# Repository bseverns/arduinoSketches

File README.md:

# Arduino Sketchbook Field Guide

Welcome to the synth lab slash robot garage. This repo is a studio notebook of quick-and-dirty experiments, but now it has a map. Use this README like a zine—skim the spreads, pick a neighborhood, and dive in with intent.

## How this sketchbook is organized
Each folder is an Arduino sketch directory. Drop one into your `sketchbook/` and the IDE will treat it as its own project. Libraries such as **Mozzi** or **Adafruit WaveHC** must already be installed in your Arduino environment.

The collections below are loose crews, not rigid taxonomies; if you discover better alignments, remix away.

If you want to organize by **progression instead of genre**, use [`docs/progression-map.md`](docs/progression-map.md). That map groups folders into likely family lines such as `greyBox_*`, `mozzi_5knob*`, `SKY_PHONE_*`, and other sketch evolutions, which is the safest way to start cleaning a repo this flat.

## New Top-Level Structure
- `experiments/`
  - Families of sketches that clearly represent iterative work.
- `projects/`
  - More complete or installation-oriented builds that have progressed beyond sketch experiments.
- `holding/`
  - Intentionally unspecific buckets for sketches worth keeping together before a better taxonomy is obvious.
- `archive/`
  - Legacy branches and older finished variants that should stay available without dominating the main map.
- `third_party/reference/`
  - Imported libraries, vendor code, and upstream projects kept for reference.
- repo root
  - Legacy standalone sketches and projects that have not been grouped yet.

### Synthesis & Sound Design
Projects that cook tones directly on the microcontroller.
- `experiments/synthesis/mozzi-controls/5knob_MozziSynth/`, `experiments/synthesis/mozzi-controls/mozzi_5knob/`, `experiments/synthesis/mozzi-controls/mozzi_5knob_L/`, `experiments/synthesis/mozzi-controls/mozzi_5knob_L_GB/`, `mozziSynth_glitch/`
  - Mozzi-powered sketches covering FM, glitchy filters, multi-knob control, and the cleaned-up FM showcase in this repo.
- `experiments/synthesis/attiny85-sound/attiny85_random_burst_drone/`, `experiments/synthesis/attiny85-sound/attiny85_dual_clock_clash/`, `experiments/synthesis/attiny85-sound/attiny85_quad_xor_drone/`,
  `experiments/synthesis/attiny85-sound/attiny85_pitch_ramp_randomizer/`, `experiments/synthesis/attiny85-sound/attiny85_three_voice_gate/`, `experiments/synthesis/attiny85-sound/attiny85_scale_sequencer/`,
  `experiments/synthesis/attiny85-sound/attiny85_random_pwm_noise/`, `experiments/synthesis/attiny85-sound/attiny85_pitch_mutator/`, `experiments/synthesis/attiny85-sound/attiny85_drum_trax/`
  - Bare-metal ATTiny85 tone experiments rescued from hash-folders; expect raw timer hacking and button-driven chaos.
- `experiments/synthesis/auduino/auduino/`, `experiments/synthesis/auduino/auduino_v5/`, `experiments/synthesis/auduino/AuduinoSequencer/`
  - Classic granular/noise textures and sequencer riffs.
- `granularSynth/`, `pdVCO/`, `avrPitchSampler/`
  - More experimental oscillators and pitch shifters.

### Samplers, Players & Shields
Boards that sling prerecorded audio or lean on helper hardware.
- `WAVshield/`, `PING_WAV/`, `Ping_baby/`, `PIR_soundie/`
  - SD-card playback patterns, button routing, and motion-triggered samples.
- `experiments/playback/sample-players/SamplerUnoPlayer/`, `experiments/playback/sample-players/SamplerUnoPlayer_test/`, `SampleRateMod/`, `sampleLauncher_neotrellis/`
  - Quick-loading sample players, rate changers, and the NeoTrellis launcher.
- `tiny85audioplayer/`
  - Tiny microcontroller players when you’re short on pins and patience.

### Sensors, Triggers & I/O
- `experiments/sensors-actuators/Blink_baby/`, `experiments/sensors-actuators/trinketInstall_baby/`, `experiments/sensors-actuators/lineIn/`, `experiments/sensors-actuators/baby_switch/`
  - Small hardware-facing sketches for trigger tests, sensor input, actuator output, and early switch prototypes.

### Rhythm, Sequencers & Generative Gizmos
Keep time, break time, or let the machine improvise.
- `experiments/sequencers/ArduinoPunk/`, `experiments/sequencers/SimpleZAR/`, `experiments/sequencers/sixteen_step_sequencer/`
  - Step-sequencer builds with explicit pattern editing, clocking, or step-based control.
- `experiments/algorithms/generativeAlgoSound/`, `experiments/algorithms/oneLineAlgo/`, `experiments/algorithms/_2noise/`
  - Algorithm-first audio and visual studies.
- `experiments/rhythm-boxes/drum8/`, `experiments/rhythm-boxes/ANDI-master/`
  - Drum-machine and loop-box style builds that are rhythm-led but not primarily note sequencers.
- `experiments/playback/shield-players/player_simple_shieldVersion/`, `experiments/playback/shield-players/player_interrupts_ShieldVersion/`
  - IRQ-friendly players useful for tempo-locked sample chops.

### Holding Area
- `holding/uncategorized/glitchamin/`, `holding/uncategorized/Musicator/`, `holding/uncategorized/mP1/`, `holding/uncategorized/IllutronBDemo0_2/`, `holding/uncategorized/Jingle_Hell__Saturnalia_/`, `holding/uncategorized/MozziSynth_example1/`
  - Real sketches worth keeping together, but not yet sorted into a more defensible family.
- `holding/modern-platformio-demos/moarknobs_button_ef_usb_midi_demo/`, `holding/modern-platformio-demos/diceloop_rough_prototype/`, `holding/modern-platformio-demos/hallway_reactor_2m/`, `holding/modern-platformio-demos/linelight_band_lamp/`, `holding/modern-platformio-demos/motorlightsound_lane_controller/`
  - Newer PlatformIO-era controller, sensor, and prototype snapshots imported from sibling repos for archival preservation before a stronger taxonomy is obvious.
- `holding/modern-platformio-demos/dust_press_minimal/`, `holding/modern-platformio-demos/horizon_minimal/`, `holding/modern-platformio-demos/rhythm_weave_minimal/`, `holding/modern-platformio-demos/tide_engine_minimal/`, `holding/modern-platformio-demos/orbit_looper_minimal/`, `holding/modern-platformio-demos/silt_minimal/`
  - Minimal Teensy Audio demo surfaces imported from sibling repos so the archive captures the small public-facing sketches as well as the larger firmware projects.
- `holding/modern-platformio-demos/dust_press_presets_demo/`, `holding/modern-platformio-demos/horizon_preset_morph/`, `holding/modern-platformio-demos/horizon_scope_demo/`, `holding/modern-platformio-demos/tide_engine_teaching_rig/`, `holding/modern-platformio-demos/tide_engine_humanize_demo/`
  - Richer teaching and bench-demo sketches imported from sibling repos once the minimal entrypoints were already preserved.

### Robotics, Kinetics & Control Surfaces
Anything that moves, senses, or bosses motors around.
- `drawBots/`, `drawBots_1/`
  - Button handling patterns and motion control for pen-plotter style bots.
- `dc_motor.ino` inside `drawBots/`, `experiments/robotics/robot-builds/realDRobot/`, `experiments/greybox/greyBox_Growser/`*
  - Reversible H-bridge driving and relay logic for more industrial builds.
- `experiments/robotics/robot-builds/OurRobot_1/`, `experiments/robotics/robot-builds/Our_Robot_01/`, `experiments/robotics/robot-builds/realDRobot/`, `experiments/robotics/relay-control/dbMSr3/`, `experiments/robotics/relay-control/dbSabertoothshield_1/`, `experiments/robotics/relay-control/dbrough/`, `experiments/robotics/relay-control/sP_relay1/`, `experiments/robotics/relay-control/sP_relay2/`, `experiments/robotics/relay-control/sP_relay3/`
  - Robot builds, relay control, and motor-driver experiments that fit better as families than one-offs.

### Named Projects & Installs
- `projects/interactive-installs/energy-light/ENERGY_1/`, `projects/interactive-installs/energy-light/Energy_TEST/`, `projects/interactive-installs/energy-light/Energy_FADE/`
  - A staged light/install line with clear progression in the names.
- `projects/interactive-installs/sky-phone/SKY_PHONE_2/`, `projects/interactive-installs/sky-phone/SKY_PHONE_FIN/`, `projects/interactive-installs/thesis-light/thesisLight/`, `projects/interactive-installs/thesis-light/thesisLightCTRL/`
  - Named installations or more complete interactive builds.
- `projects/personal-builds/mim/MiM_1/`, `projects/personal-builds/sproject/Sproject_1/`
  - Prior personal projects that belong in the project layer rather than the experiment layer.

### Reference Dumps & Vendor Libraries
- `third_party/reference/AdafruitAudio-master/`, `third_party/reference/Adafruit_NeoTrellisM4-master/`, `third_party/reference/Arduinoboy-master/`, `third_party/reference/jan_ostmans_synths-master/`
  - Mostly upstream copies; treat them as reference manuals.
- `third_party/reference/DuinoTune-master/`, `third_party/reference/PJRCAudio-master/`, `third_party/reference/AttinySound-master/`, `third_party/reference/Mozzi/`, `third_party/reference/wavehc/`
  - Utility toolkits that underpin several sketches.

### Notes, Docs & Ephemera
- `docs/`
  - Former stray PDFs now corralled into a single folder.
  - See `docs/showcase.md` for wiring guides + BOMs on the crowd-pleasers.
- `Notes_keke_siren/`, `ReferanceSketch/`, `projects/interactive-installs/sky-phone/SKY_PHONE_2/`, `projects/interactive-installs/sky-phone/SKY_PHONE_FIN/`
  - Mixed notes and iterations. Expect loose ends.
- `archive/legacy-finals/son-build/The_Son_final/`, `archive/legacy-finals/son-build/The_Son_final_a/`
  - Older final-branch snapshots kept around for history, not active browsing.

\* Many of these builds assume external motor drivers, relays, or sensors. Read the header comments in each sketch for wiring specifics before soldering anything permanent.

## Quick-start checklists
1. **Pick a theme above** and copy that folder to your Arduino sketchbook.
2. **Install dependencies** (Mozzi, WaveHC, Sabertooth, etc.) via the Arduino Library Manager or from the copies in `third_party/reference/`.
3. **Check pin assignments** in the `.ino` file comments and adjust for your hardware.
4. **Prototype fast**. This is a playground—fork the sketch, twist a knob, record what happens.

## Where to explore next
- Tighten the best-performing sketches into showcase-ready demos with photos or wiring diagrams. `docs/showcase.md` has TODO slots waiting for media drops.
- Document unexpected tricks (timer sharing, ISR gotchas) directly in the sketches.
- Trade polished recordings for commit history: drop audio snippets or GIFs into `docs/` to complement the code. Call your shot with TODO notes until the binary files land.
- Keep moving low-ambiguity families first; leave one-off sketches at the repo root until the domain or lineage is actually clear.

Questions? Crack open the serial monitor, read the comments, and don’t be afraid to get weird—but keep it useful.

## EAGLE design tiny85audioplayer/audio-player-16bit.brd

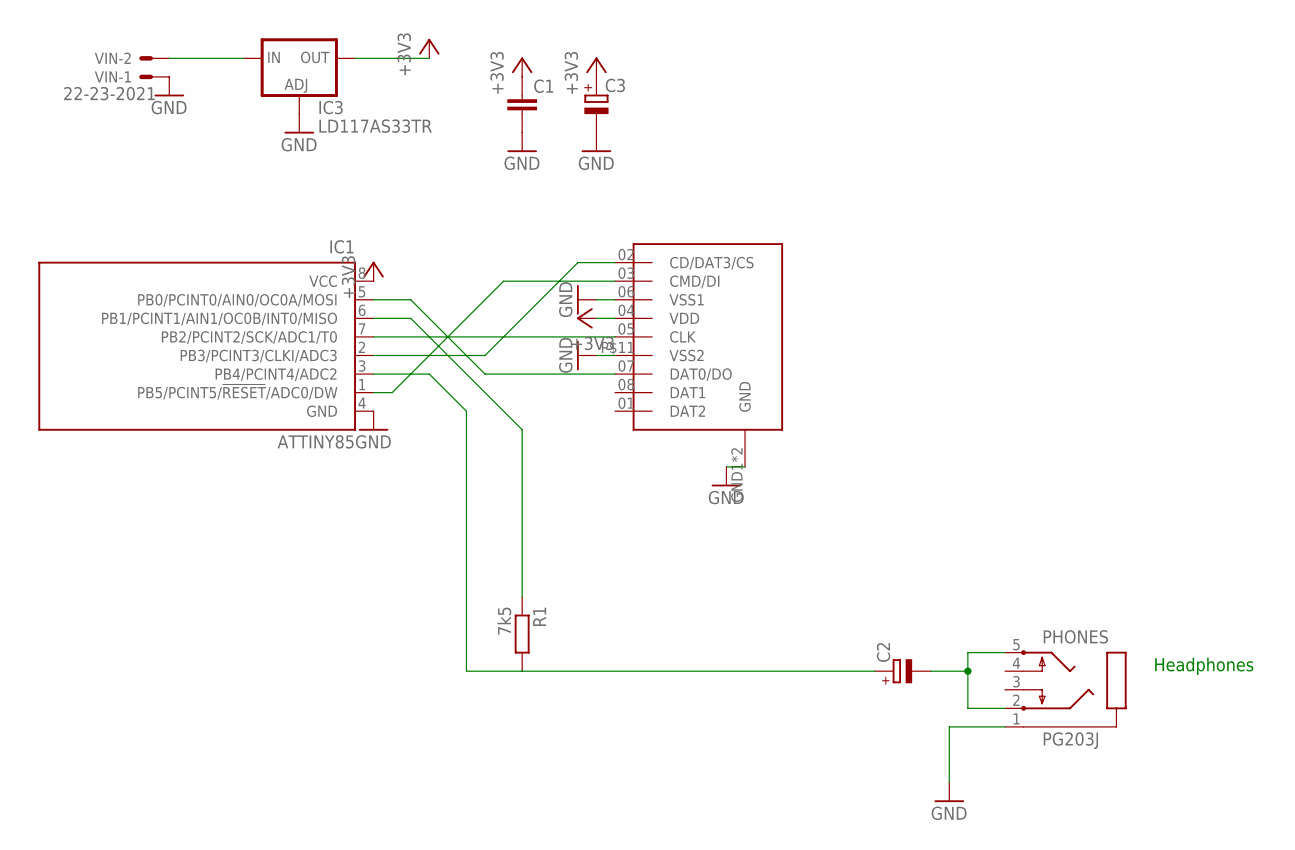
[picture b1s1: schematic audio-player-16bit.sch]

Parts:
C1: C-EUC1206; C1206
C2: CPOL-EU140CLH-1014; 140CLH-1014
C3: CPOL-EUCT3528; CT3528
IC1: ATTINY85; DIL08
IC3: LD117AS33TR; SOT223
PHONES: PG203J
R1: 7k5; R1206
U$1: MICROSD; SCHD3A0100
VIN: 22-23-2021

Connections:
+3V3: C1.1, C3.+, IC1.8 (VCC), IC3.4 (OUT), U$1.04 (VDD)
GND: C1.2, C3.-, IC1.4 (GND), IC3.1 (ADJ), PHONES.1, U$1.06 (VSS1), U$1.GND1 (GND), U$1.GND2 (GND), U$1.P$11 (VSS2), VIN.1
unnamed: IC1.2 (PB3/PCINT3/CLKI/ADC3), U$1.02 (CD/DAT3/CS)
unnamed: IC1.6 (PB1/PCINT1/AIN1/OC0B/INT0/MISO), R1.1
unnamed: IC1.7 (PB2/PCINT2/SCK/ADC1/T0), U$1.05 (CLK)
unnamed: C2.+, IC1.3 (PB4/PCINT4/ADC2), R1.2
unnamed: IC1.1 (PB5/PCINT5/!RESET!/ADC0/DW), U$1.03 (CMD/DI)
unnamed: IC1.5 (PB0/PCINT0/AIN0/OC0A/MOSI), U$1.07 (DAT0/DO)
unnamed: IC3.3 (IN), VIN.2
unnamed: C2.-, PHONES.2, PHONES.5

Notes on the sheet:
Headphones

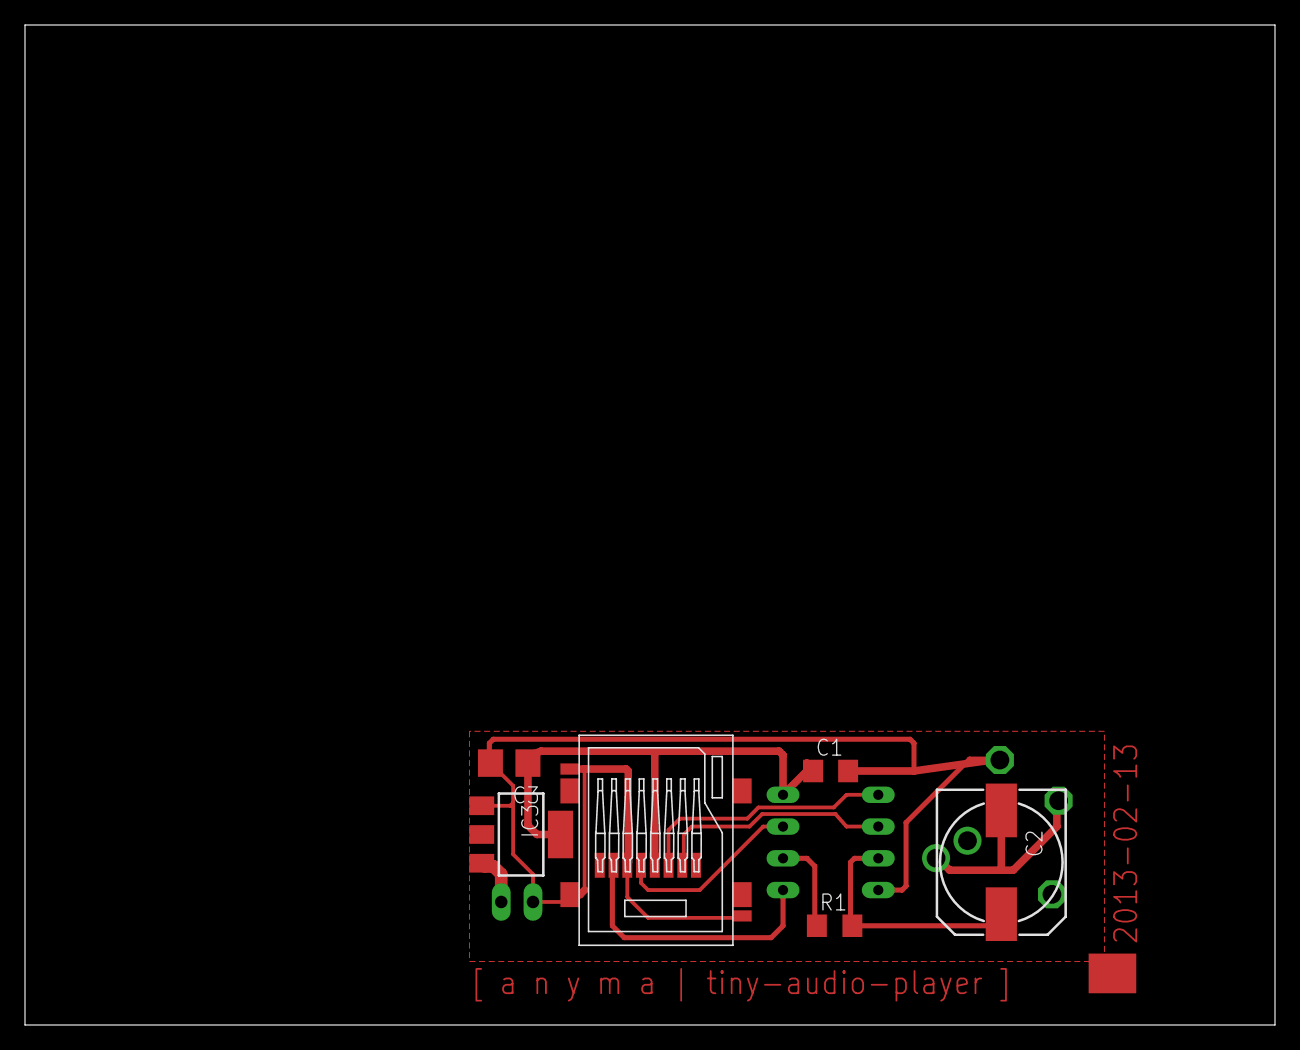
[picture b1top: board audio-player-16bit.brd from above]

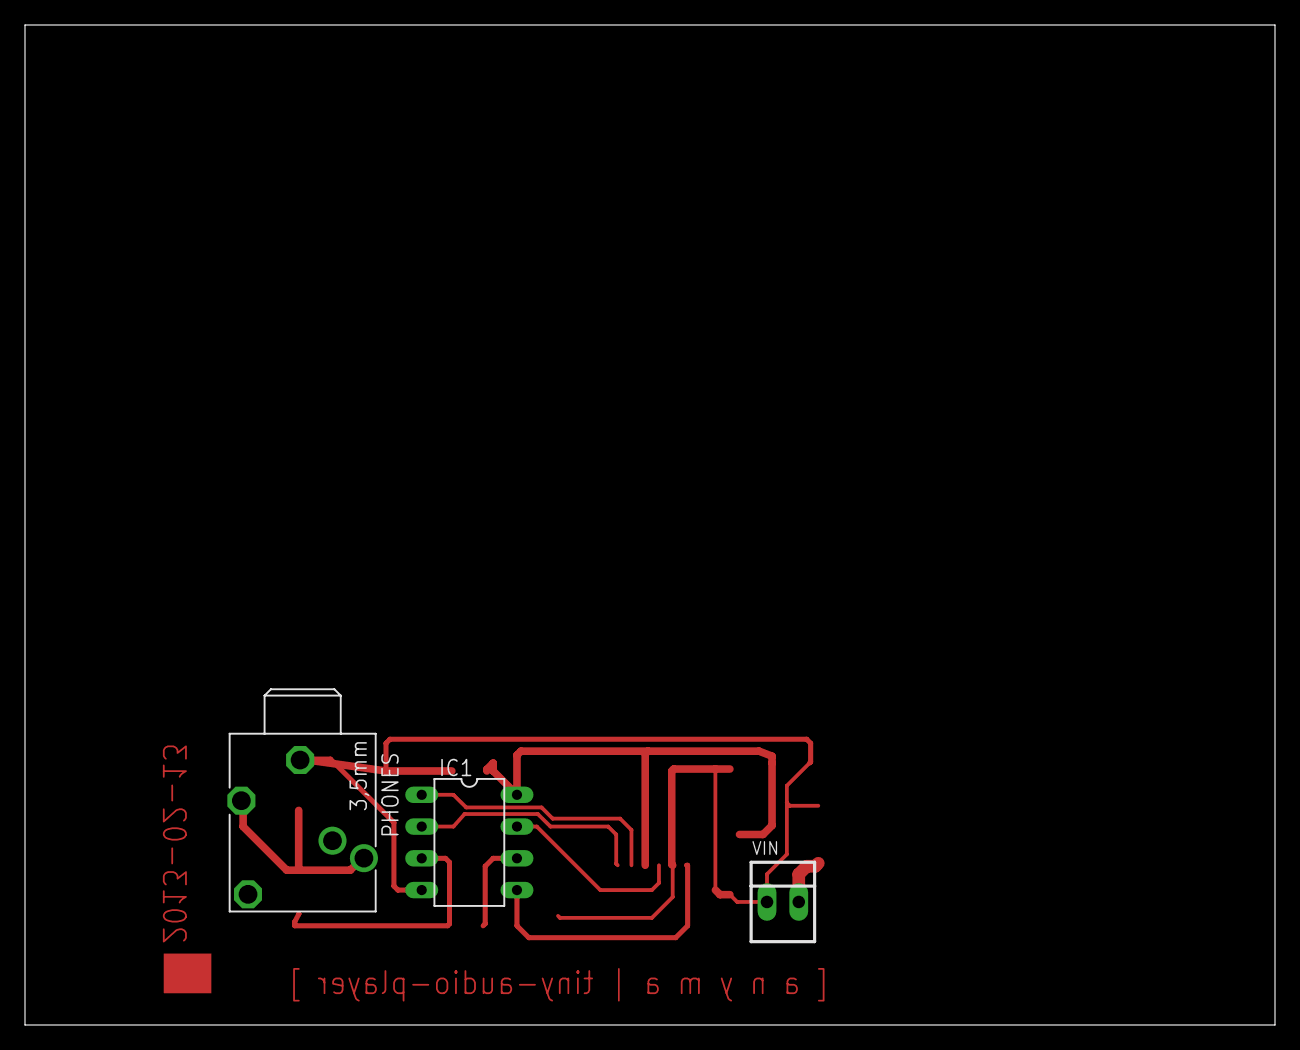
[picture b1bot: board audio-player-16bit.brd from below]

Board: 2 copper layers, 100.0 x 80.0 mm, 9 parts (3 on the bottom side), 10 nets.

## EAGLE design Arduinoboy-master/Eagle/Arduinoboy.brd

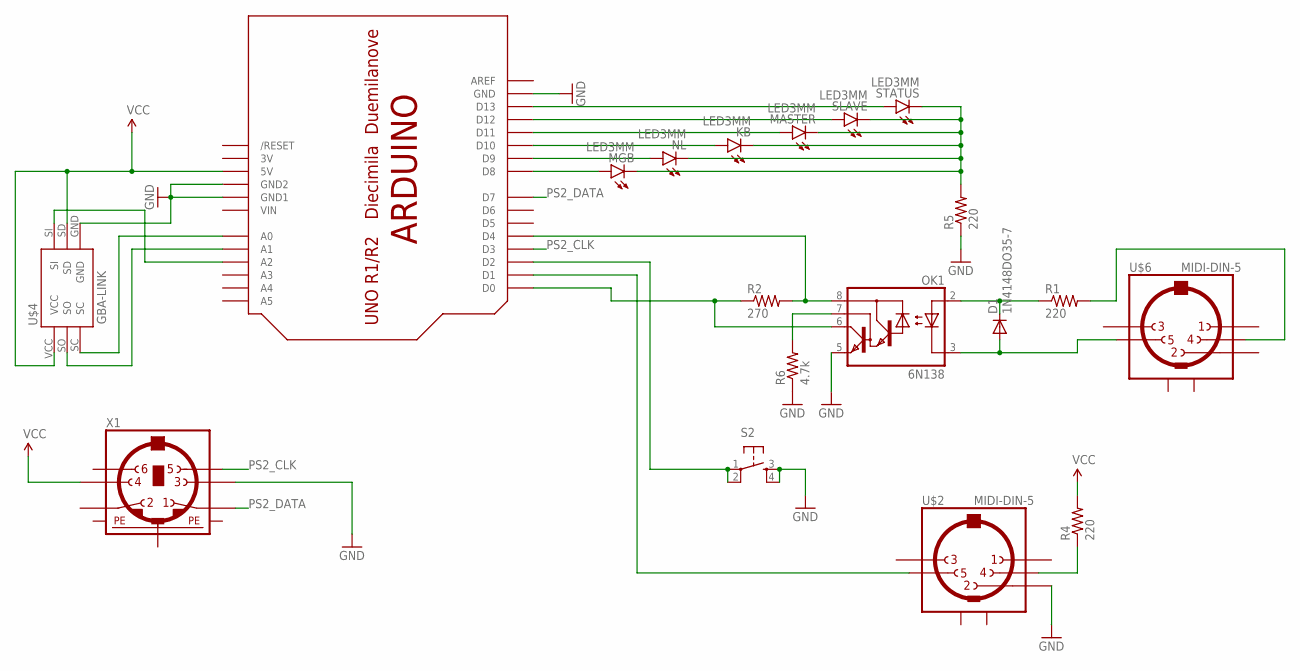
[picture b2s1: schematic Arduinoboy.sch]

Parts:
D1: 1N4148DO35-7; DO35-7
KB: LED3MM
MASTER: LED3MM
MGB: LED3MM
NL: LED3MM
OK1: 6N138; DIL08
R1, R4, R5: 220; AXIAL-0.3
R2: 270; AXIAL-0.3
R6: 4.7k; AXIAL-0.3
S2: TAC_SWITCHPTH; TACTILE-PTH
SLAVE: LED3MM
STATUS: LED3MM
U$2, U$6: MIDI-DIN-5
U$3: ARDUINOUNO; ARDUINO
U$4: GBA-LINK
X1: MINI_DIN_6; M_DIN6

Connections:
3V: U$3.3V
GND: OK1.5 (GND), R5.P$1 (1), R6.P$1 (1), S2.3, S2.4, U$2.2, U$3.GND, U$3.GND1, U$3.GND2, U$4.GND, X1.3
unnamed: D1.C, OK1.2 (A), R1.P$1 (1)
unnamed: D1.A, OK1.3 (C), U$6.5
unnamed: R4.P$1 (1), U$2.4
unnamed: MGB.A, U$3.D8
unnamed: U$2.5, U$3.D1
unnamed: NL.A, U$3.D9
unnamed: OK1.8 (VCC), R2.P$2 (2), U$3.D4
unnamed: OK1.6 (VO), R2.P$1 (1), U$3.D0
unnamed: KB.A, U$3.D10
unnamed: MASTER.A, U$3.D11
unnamed: SLAVE.A, U$3.D12
unnamed: STATUS.A, U$3.D13
unnamed: KB.K (C), MASTER.K (C), MGB.K (C), NL.K (C), R5.P$2 (2), SLAVE.K (C), STATUS.K (C)
unnamed: OK1.7 (VB), R6.P$2 (2)
unnamed: U$3.A0, U$4.SC
unnamed: R1.P$2 (2), U$6.4
unnamed: S2.1, S2.2, U$3.D2
unnamed: U$3.A1, U$4.SO
unnamed: U$3.A2, U$4.SI
PE1: X1.SH1 (PE1)
PE2: X1.SH2 (PE2)
PE3: X1.SH3 (PE3)
PS2_CLK: U$3.D3, X1.5
PS2_DATA: U$3.D7, X1.1
VCC: R4.P$2 (2), U$3.5V, U$4.SD, U$4.VCC, X1.4
VIN: U$3.VIN

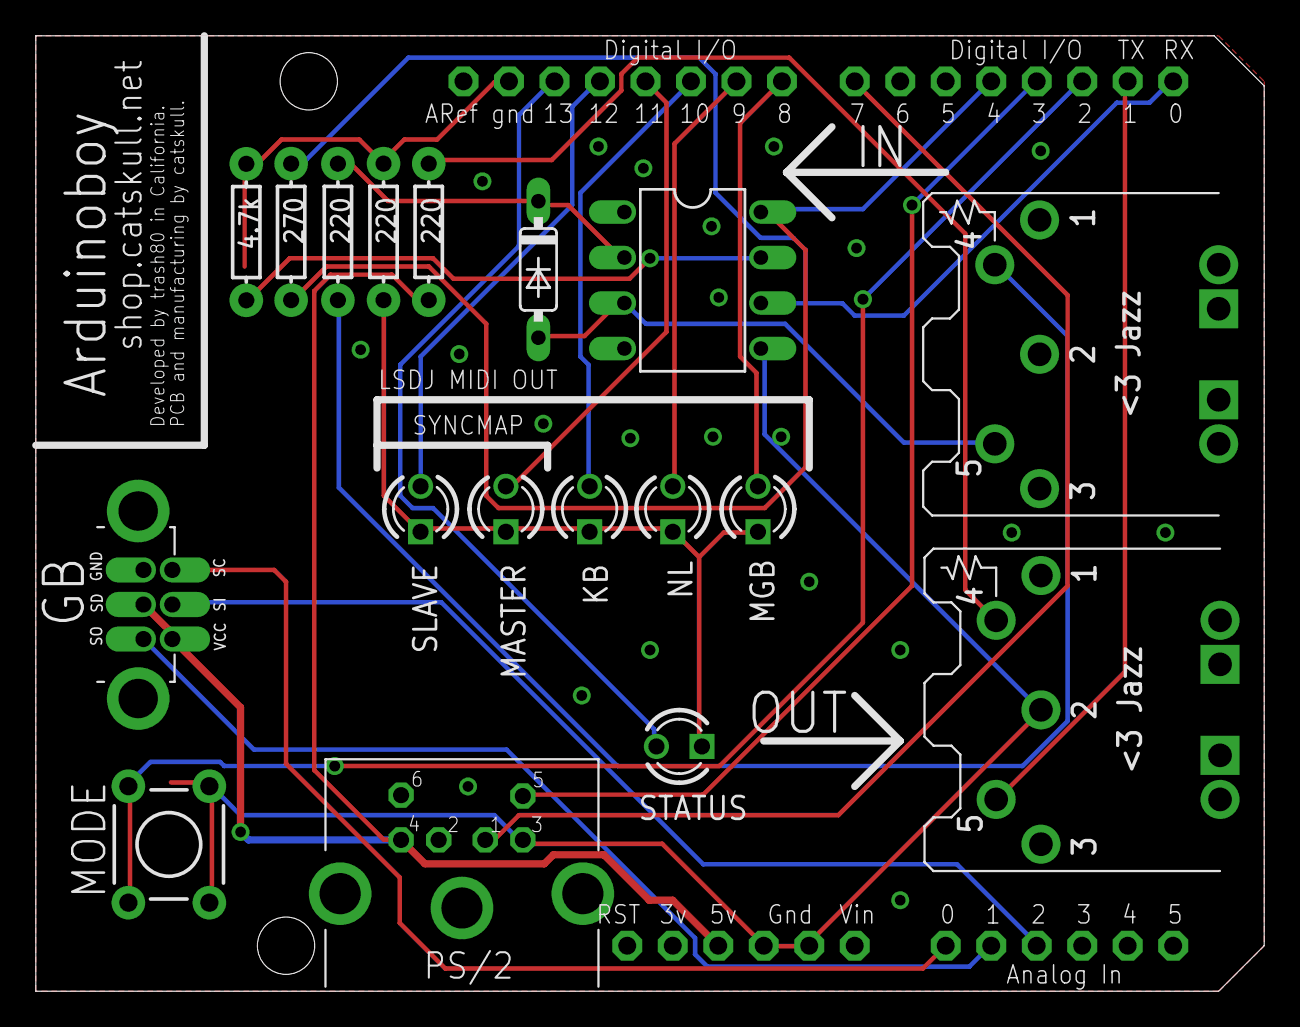
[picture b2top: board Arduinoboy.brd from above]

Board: 2 copper layers, 68.6 x 53.3 mm, 19 parts (0 on the bottom side), 23 nets.

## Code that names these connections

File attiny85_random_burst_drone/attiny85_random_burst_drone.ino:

/*
  ATTiny85 Random Burst Drone
  ---------------------------
  Ports PB3 and PB4 (Arduino pins 3 and 4 on the Tiny board) spit alternating bursts.
  Buttons on PB0/PB1/PB2 skew the random clock, pitch, and reset behaviour.
  Restored from the original hash-named sketch for clarity.
*/

#include <avr/interrupt.h>
#include <inttypes.h>
#include <avr/io.h>
#include <math.h>

void delayms(uint16_t millis);
void delayuss(unsigned int micros);
inline unsigned long Random(void);

int main()
{
        DDRB  = (1 << 3) | (1 << 4);
        PORTB = (1 << 0) | (1 << 1);

        unsigned int randommer = 40;
        unsigned int playframes = 1000;
        unsigned int waitframes = 1000;
        unsigned int frame = 0;
        unsigned int pitch = 0;

        while (1)
        {
                if ( frame < playframes)
                {
                        PORTB |= (1 << 3) | (1 << 4);
                        delayuss(Random()/randommer);

                        PORTB &= ~((1 << 3) | (1 << 4));
                        delayuss(Random()/randommer);
                        frame++;
                }

                else if (frame - playframes <  waitframes)
                {
                        PORTB |= (1 << 3) | (1 << 4);
                        delayuss(pitch);

                        PORTB &= ~((1 << 3) | (1 << 4));
                        delayuss(pitch);
                        frame++;
                }

                else
                        frame = 0;

                if ((PINB & 1) == 0)
                {
                        if (randommer > 3)
                                randommer--;
                        if (pitch < 2000)
                        {
                                pitch++;
                        }
                        playframes = Random()/200;
                        waitframes = Random()/200;
                }
                if ((PINB & 2) == 0)
                {
                        if (randommer < 10000)
                                randommer+= 2;
                        if (pitch > 20)
                        {
                                pitch--;
                        }
                        playframes = Random()/200;
                        waitframes = Random()/200;
                }

                if ((PINB & 3) == 0)
                {
                        randommer = Random()/200;
                        pitch = Random()/200;
                        playframes = Random()/200;
                        waitframes = Random()/200;
                }

        }

        return 0;
}

/* at 8 MHz we get 1us per 8 instructions */
inline void delayus() { asm volatile("nop\nnop\nnop\nnop\n"
                                     "nop\nnop\nnop\nnop"); }


// Resources

void delayuss(unsigned int micros)
{
        while (micros)
        {
                delayus();
                micros--;
        }
}

void delayms(uint16_t millis) {
  uint16_t loop;
  while ( millis ) {
    loop = 100;
    while (loop) {
      /* 20us of delays */
      delayus(); delayus(); delayus(); delayus(); delayus();
      delayus(); delayus(); delayus(); delayus(); delayus();
      loop --;
    }
    millis--;
  }
}

unsigned long NextRandom = 1;
inline unsigned long Random(void)
{
   NextRandom = NextRandom * 1103515245 + 12345;
   return ((NextRandom >> 16) & 32767);
}

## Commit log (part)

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2025-09-15 init
2025-09-15 moar
2025-11-13 Restore ATTiny hash sketches with descriptive names
2025-11-13 Add README for MozziSynth example with hardware notes
2025-11-13 Document drawBots motor and button wiring
2025-11-13 Document Grey Box FM stack
2025-11-13 Document showcase builds and media TODOs
2025-11-28 .gitignore
2026-01-05 Add .DS_Store files to .gitignore
    Updated .gitignore to exclude .DS_Store files from the root and subdirectories, preventing accidental commits of macOS metadata files.
2026-03-14 Reorganize sketches into domain folders and clean artifacts
2026-04-05 Archive modern demo sketches and expand showcase

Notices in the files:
parts and their libraries:
SparkFun-Resistors: Licensing: Creative Commons ShareAlike 4.0 International - https://creativecommons.org/licenses/by-sa/4.0
